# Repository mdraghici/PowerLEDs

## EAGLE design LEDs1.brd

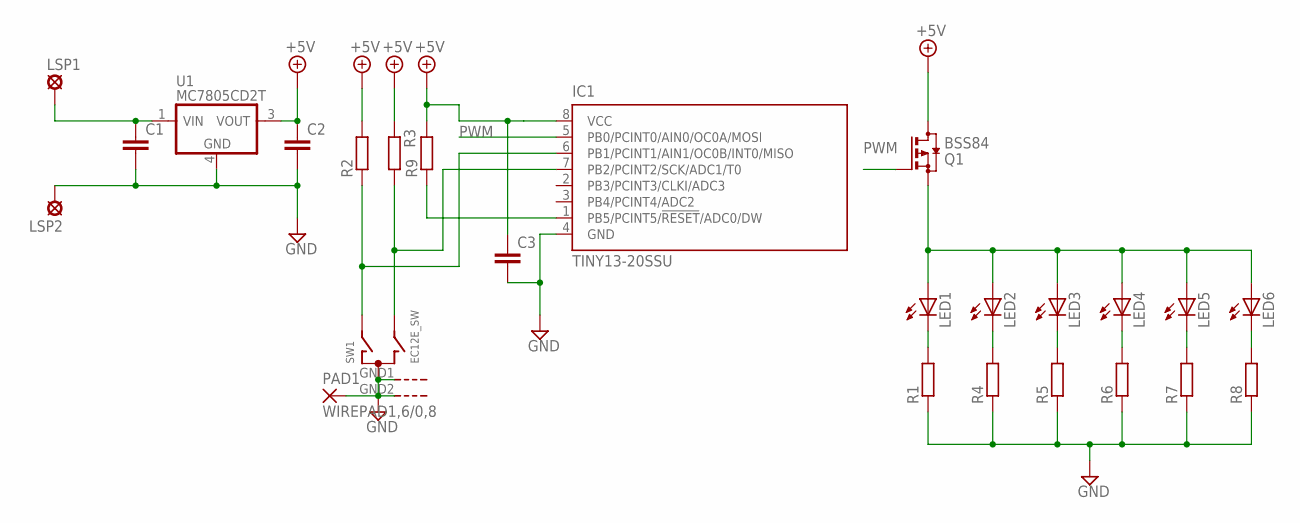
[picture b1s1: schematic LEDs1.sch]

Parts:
C1, C2, C3: C-EUC1206K; C1206K
IC1: TINY13-20SSU; 8S1
LED1, LED2, LED3, LED4, LED5, LED6: LED-2AC-CP41B-WES; CP41B
LSP1, LSP2: LSP10
PAD1: WIREPAD1,6/0,8; 1,6/0,8
Q1: BSS84; SOT23
R1, R4, R5, R6, R7, R8, R9: R-EU_M0805; M0805
R2, R3: R-EU_M1206; M1206
SW1: EC12E_SW; ALPS_EC12E_SW
U1: MC7805CD2T; D2PAK-3

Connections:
+5V: C2.1, C3.1, IC1.8 (VCC), Q1.3 (D), R2.2, R3.1, R9.2, U1.3 (VOUT)
GND: C1.2, C2.2, C3.2, IC1.4 (GND), LSP2.MP, PAD1.1, R1.1, R4.1, R5.1, R6.1, R7.1, R8.1, SW1.C, SW1.GND1 (G), SW1.GND2 (G), U1.4 (GND)
unnamed: C1.1, LSP1.MP, U1.1 (VIN)
unnamed: IC1.6 (PB1/PCINT1/AIN1/OC0B/INT0/MISO), R2.1, SW1.A
unnamed: IC1.7 (PB2/PCINT2/SCK/ADC1/T0), R3.2, SW1.B
unnamed: IC1.1 (PB5/PCINT5/!RESET!/ADC0/DW), R9.1
unnamed: LED1.2 (A), LED1.3 (A), LED2.2 (A), LED2.3 (A), LED3.2 (A), LED3.3 (A), LED4.2 (A), LED4.3 (A), LED5.2 (A), LED5.3 (A), LED6.2 (A), LED6.3 (A), Q1.2 (S)
unnamed: LED1.1 (C), LED1.4 (C), R1.2
unnamed: LED2.1 (C), LED2.4 (C), R4.2
unnamed: LED3.1 (C), LED3.4 (C), R5.2
unnamed: LED4.1 (C), LED4.4 (C), R6.2
unnamed: LED5.1 (C), LED5.4 (C), R7.2
unnamed: LED6.1 (C), LED6.4 (C), R8.2
PWM: IC1.5 (PB0/PCINT0/AIN0/OC0A/MOSI), Q1.1 (G)

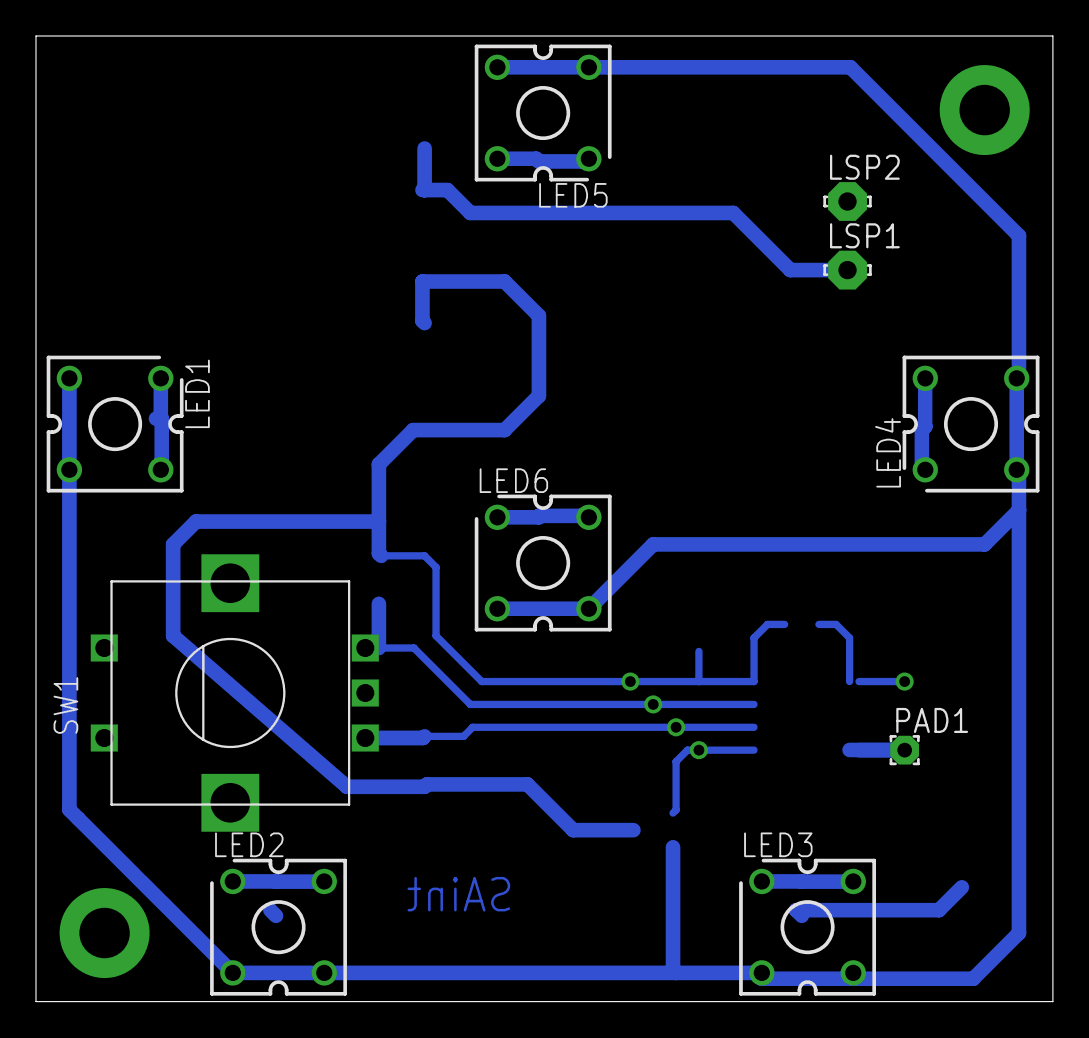
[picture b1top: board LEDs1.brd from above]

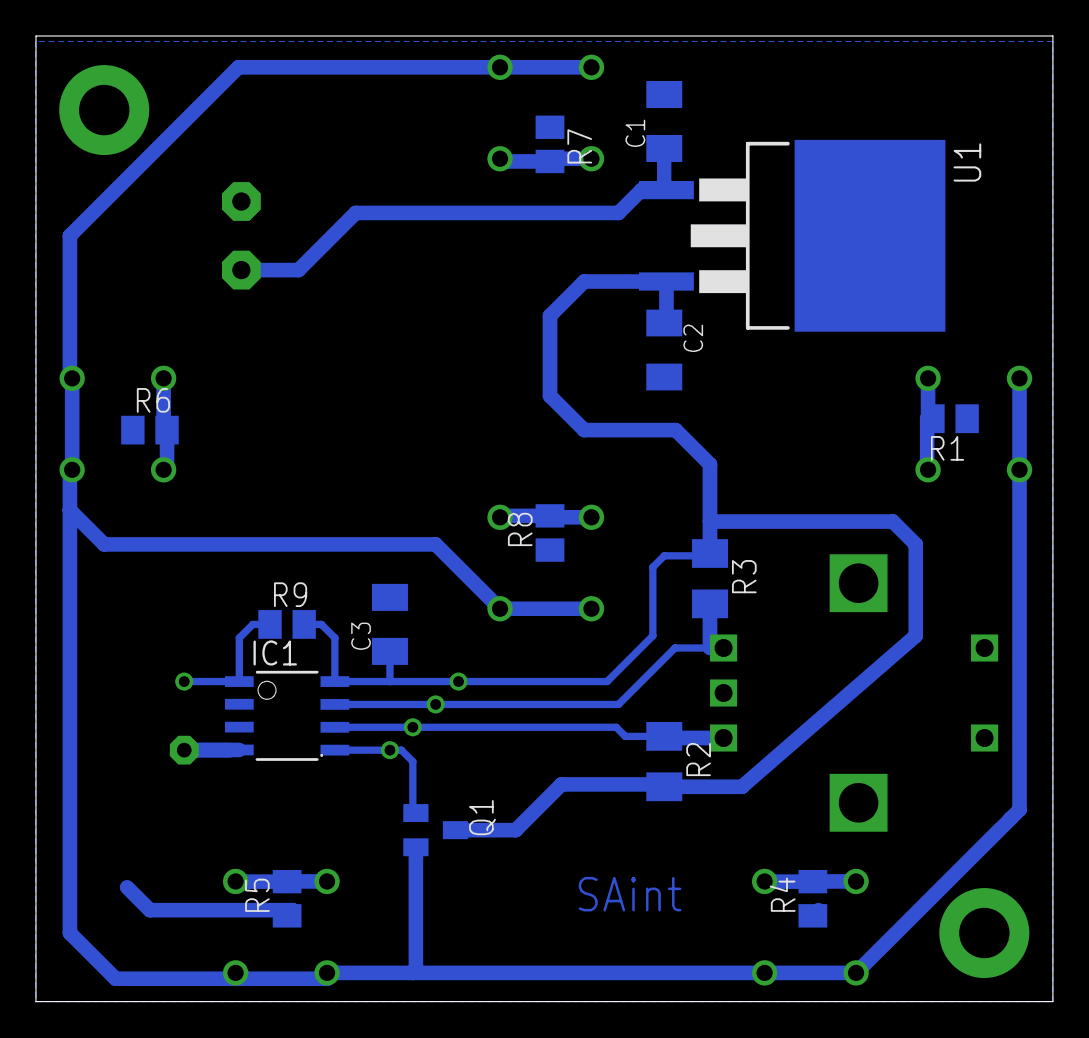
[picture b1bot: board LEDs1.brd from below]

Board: 2 copper layers, 56.5 x 53.6 mm, 25 parts (15 on the bottom side), 14 nets.

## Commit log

2014-02-05 Power LED schematics
